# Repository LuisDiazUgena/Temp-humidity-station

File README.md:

# Temp-humidity-station

Temperature and humidity station with RF communications between stations.

###Sketchs

There are two sketchs:

*emmiter.ino* that manages the emiter side (it's uses a lm35 temperature sensor and a FS1000A rf emitter.

*reciever.ino* manages the reciever side. It uses a LCD 20x4 module to display data, dht22 to display temperature & humidity data, XY-MK-5V RF module to communicate with emiter module.

---

### Hardware

BOM, schematichs and pcb layaouts comming soon.

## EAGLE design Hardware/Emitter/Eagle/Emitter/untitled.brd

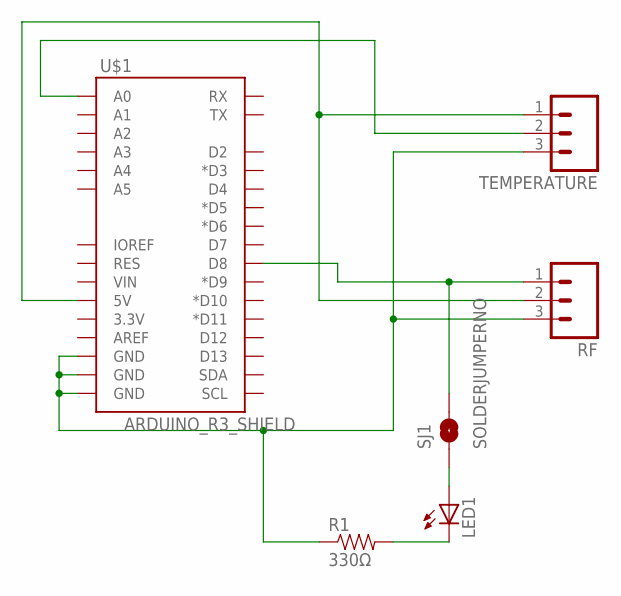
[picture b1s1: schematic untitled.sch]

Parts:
LED1: LED5MM
R1: 330Ω; AXIAL-0.3
RF: M03LONGPADS; 1X03_LONGPADS
SJ1: SOLDERJUMPERNO; SJ_2S-NO
TEMPERATURE: M03LONGPADS; 1X03_LONGPADS
U$1: ARDUINO_R3_SHIELD; UNO_R3_SHIELD

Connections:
unnamed: LED1.A, SJ1.1
unnamed: R1.P$1 (1), RF.3, TEMPERATURE.3, U$1.GND@0 (GND), U$1.GND@1 (GND), U$1.GND@2 (GND)
unnamed: RF.1, SJ1.2, U$1.D8
unnamed: TEMPERATURE.2, U$1.A0
unnamed: LED1.K (C), R1.P$2 (2)
unnamed: RF.2, TEMPERATURE.1, U$1.5V

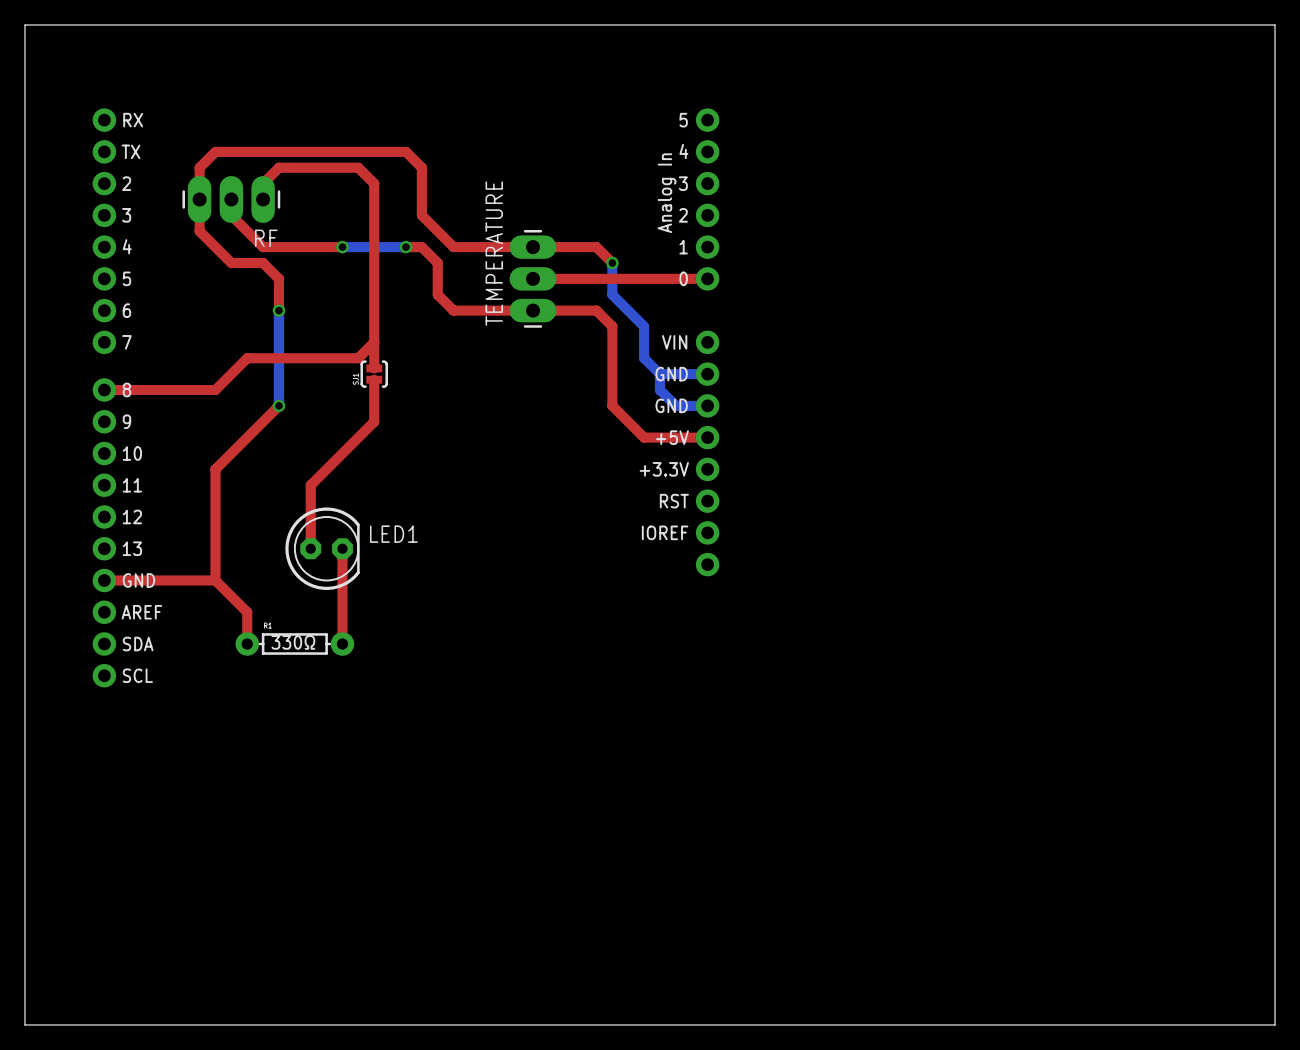
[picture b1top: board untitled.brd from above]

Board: 2 copper layers, 100.0 x 80.0 mm, 6 parts (0 on the bottom side), 6 nets.

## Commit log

2015-03-08 Add reciever sketch
2015-03-08 Added emitter.ino file
2015-03-08 Added changes to developer info and license
2015-03-08 Removed innecesary code
2015-03-08 Modified Readme.md
2015-03-08 added schematics and board files

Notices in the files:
parts and their libraries:
SparkFun-Resistors: Licensing: Creative Commons ShareAlike 4.0 International - https://creativecommons.org/licenses/by-sa/4.0
